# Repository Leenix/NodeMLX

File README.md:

# NodeMLX
Embedded Arduino-based thermal tracking with a NodeMCU and a Melexis MLX90621 thermopile array sensor.

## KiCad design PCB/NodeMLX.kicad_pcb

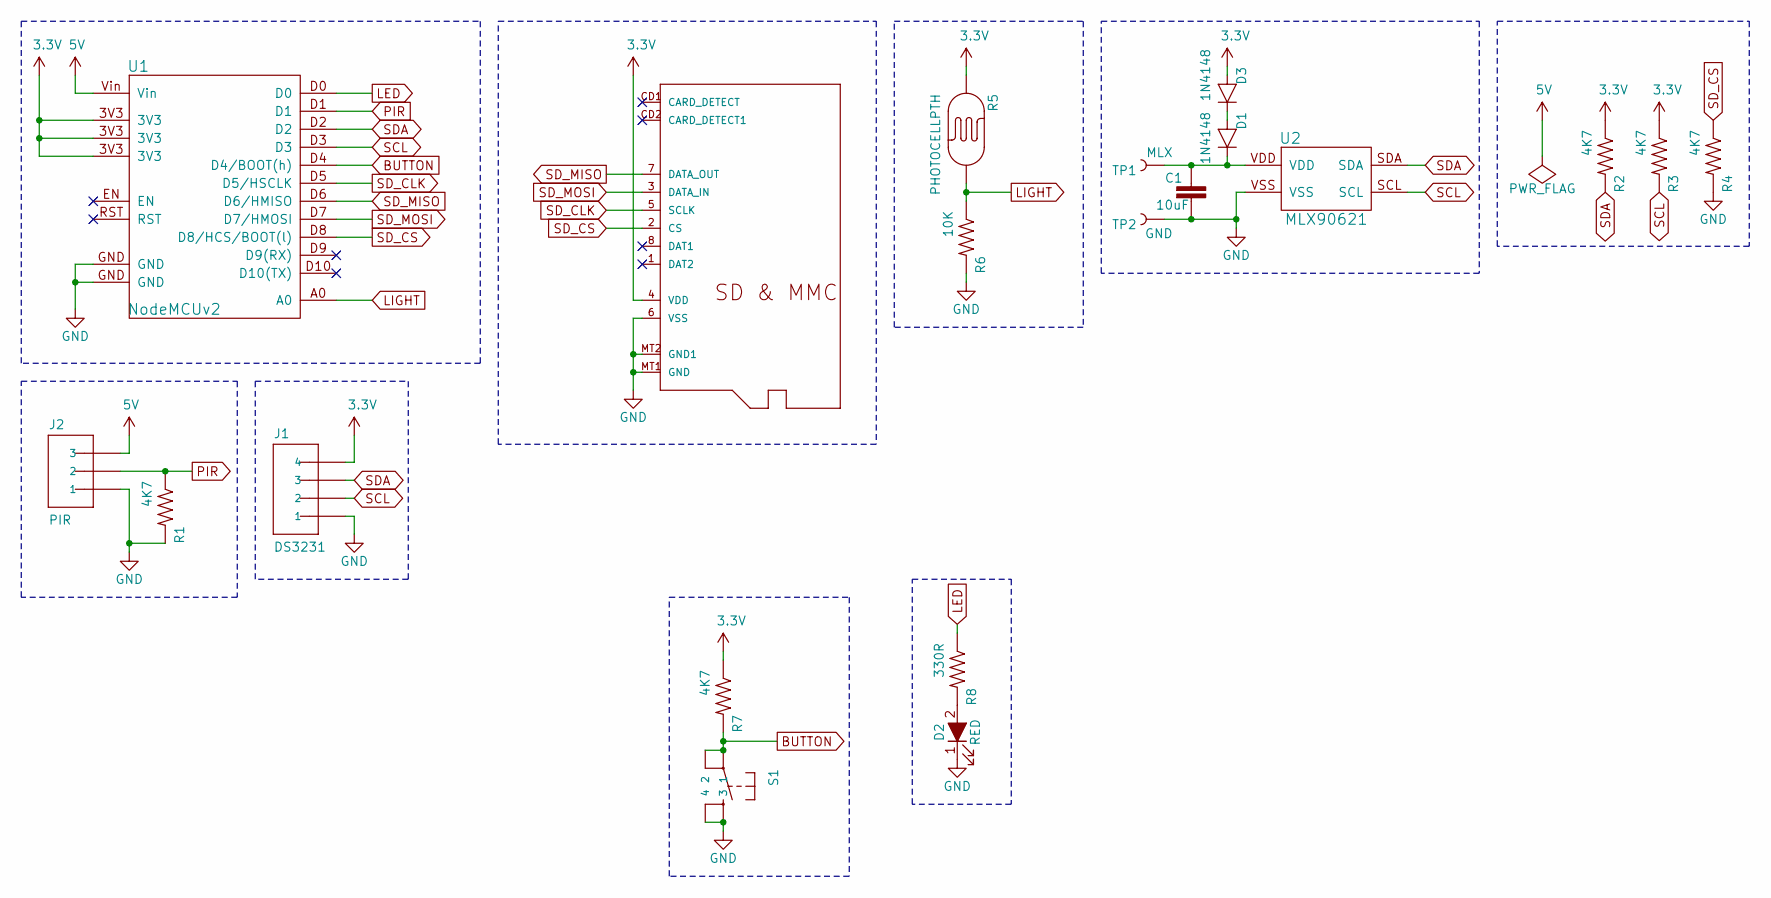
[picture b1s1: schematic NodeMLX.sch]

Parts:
C1: 10uF; C_1206
D1, D3: 1N4148; D_SOD-123
D2: RED; LED_1206
J1: DS3231; Pin_Header_Angled_1x04_Pitch2.54mm
J2: PIR; Pin_Header_Angled_1x03_Pitch2.54mm
M1: MICROSD
R1, R2, R3, R4, R7: 4K7; R_1206
R5: PHOTOCELLPTH; PHOTOCELL
R6: 10K; R_1206
R8: 330R; R_1206
S1: TAC_SWITCHSMD; TACTILE-SWITCH-SMD
TP1: MLX; PAD.02X.02
TP2: GND; PAD.02X.02
U1: NodeMCUv2; nodemcuv2
U2: MLX90621; mlx90621

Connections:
3.3V: D3.2 (A), J1.4, M1.4 (VDD), R2.1, R3.1, R5.1, R7.1, U1.3V3
5V: J2.3, U1.Vin
BUTTON: R7.2, S1.1, S1.2, U1.D4 (D4/BOOT(h))
GND: C1.2, D2.1 (K), J1.1, J2.1, M1.6 (VSS), M1.MT1 (GND), M1.MT2 (GND1), R1.2, R4.2, R6.2, S1.3, S1.4, TP2.P$1, U1.GND, U2.VSS
LED: R8.1, U1.D0
LIGHT: R5.2, R6.1, U1.A0
unnamed: C1.1, D1.1 (C), TP1.P$1, U2.VDD
unnamed: D1.2 (A), D3.1 (C)
unnamed: D2.2 (A), R8.2
PIR: J2.2, R1.1, U1.D1
SCL: J1.2, R3.2, U1.D3, U2.SCL
SDA: J1.3, R2.2, U1.D2, U2.SDA
SD_CLK: M1.5 (SCLK), U1.D5 (D5/HSCLK)
SD_CS: M1.2 (CS), R4.1, U1.D8 (D8/HCS/BOOT(l))
SD_MISO: M1.7 (DATA_OUT), U1.D6 (D6/HMISO)
SD_MOSI: M1.3 (DATA_IN), U1.D7 (D7/HMOSI)

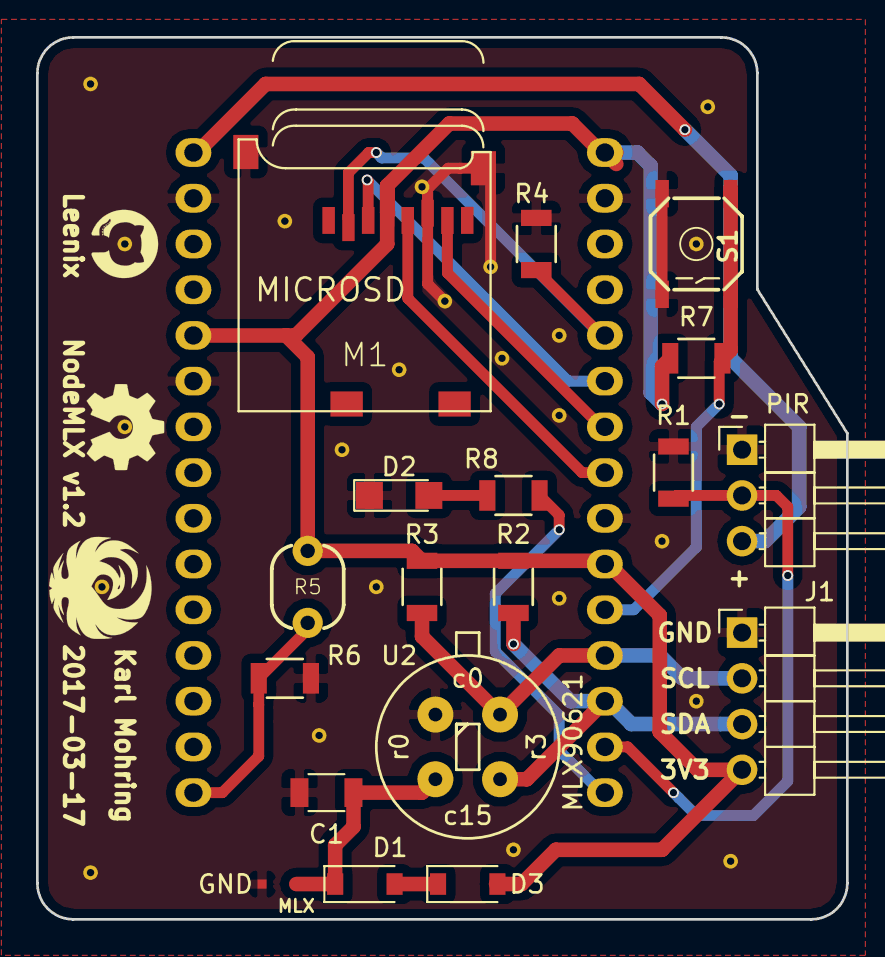
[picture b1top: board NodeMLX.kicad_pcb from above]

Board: 2 copper layers, 45.0 x 49.0 mm, 20 parts (1 on the bottom side), 16 nets.

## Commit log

2017-01-13 Added PCB files
2017-01-23 Added minimum variance for detection
2017-02-03 Version 1.1 update - Lots of changes to sensors + Firmware updated to v1.1 to suit the extra kit + WiFi uploading added to firmware + Add SD card socket + Added RTC + Added LDR light sensor + Added b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
2017-02-24 Cut down redundant code
2017-03-20 Fixed PCB. Added html generators for live map
2017-03-23 Updated documentation
2017-04-28 Fixed PCB; added callbacks
2017-06-06 Massive changes. - Added web interface to change all tracking variables - All tracking variables are now mutable at runtime - Reworked tracking penalties - Reworked track reporting with callbacks - D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
2017-06-07 Added last tracked blobs to web interface - Difference is now calculated using class variables
2017-06-08 - Fixed Wifi connection bug - Resorted penalties - Hopefully fixed direction penalty bug
2017-06-13 2017-06-11 Weekend overpass test configuration
2017-06-13 Added a fuzz factor to pixel adjacency calculation Hopefully this smooths out blobs a bit
2017-08-24 Added dead frame penalty to tracking - Lost blobs that disappear between frames should now be recoverable
2017-08-25 Fixed version numbering
2017-08-25 TrackedBlob file done fucked itself
2017-08-25 Merged dead frame tracking - Colourised main menu - Added background frame monitoring - Added processing frame rate - Fixed bug with setting dead frame limit - Fixed bug copying dead frame tracking w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
2017-08-25 Improved WiFi reliability - Automatic keepalives and reconnection checks
2017-08-28 Added dead frame info to debug
2017-11-02 Last push before merge
